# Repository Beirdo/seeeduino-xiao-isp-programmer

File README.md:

seeeduino-xiao-isp-programmer

As I have many Arduino-capable boards in the works, I once again felt the need
for an ISP-based programmer.  I used to use a buspirate, but I don't know 
where it is right now.

This design uses the new Seeeduino XIAO modules.  See:
https://wiki.seeedstudio.com/Seeeduino-XIAO for details.  They are obtainable
very affordably here:
https://www.amazon.com/dp/B08745JBRP/

The v2.0 circuit boards are available to get created at:
https://oshpark.com/shared_projects/VRfrdtNt

I will upload a Digikey-compatible BOM soon, although there are not many parts
here:
* 2 * 10k resistor (0805)
* 1 * MMBT3904 NPN Transistor (SOT23-3)
* 1 * TXB0104PW Bidirectional Level Shifter (TSSOP14)
* 1 * 2x3 0.100" pitch male pin connector for use with a ribbon cable
* 1 * Seeeduino XIAO module (surface mount solder it on using the castellations)

This design is Open Hardware, and the code here is adapted from the ArduinoISP
"example" that comes with the Arduino IDE.  The main changes will be mapping
the IOs for the LEDs correctly, the positive logic reset signal, and the output
enable for the level shifter.

The ISP connector is using 5V signalling, and the XIAO internally uses 3.3V
signalling.  Rather than blow it up over time, I have put in the proper level
shifting on all the data lines (SPI + reset line).  The reset line is using
an open collector setup with a pullup to +5V.  All I/O (at both voltages) are
tristated by default in the level shifter, and are only enabled once the output
enable is driven high (there is a pulldown to make sure it floats low when not
actively being driven).

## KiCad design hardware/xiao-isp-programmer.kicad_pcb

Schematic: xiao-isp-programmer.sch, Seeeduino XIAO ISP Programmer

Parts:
J1: Conn_02x03_Odd_Even; PinHeader_2x03_P2.54mm_Vertical
Q1: MMBT3904; SOT-23
R1, R2: 10k; R_0805_2012Metric_Pad1.20x1.40mm_HandSolder
U1: SeeeduinoXIAO; Seeeduino XIAO-MOUDLE14P-2.54-21X17.8MM
U2: TXB0104PW; TSSOP-14_4.4x5mm_P0.65mm

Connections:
+3V3: U1.12, U2.1 (VCCA)
+5V: J1.2, R1.1, U1.14, U2.14 (VCCB)
GND: J1.6, Q1.2 (E), R2.2, U1.13, U2.7 (GND)
MISO: J1.1, U2.12 (B2)
MOSI: J1.4, U2.13 (B1)
unnamed: Q1.1 (B), U2.10 (B4)
unnamed: U1.9, U2.4 (A3)
unnamed: U1.10, U2.3 (A2)
unnamed: U1.11, U2.2 (A1)
OE: R2.1, U1.3, U2.8 (OE)
RESET: U1.2, U2.5 (A4)
SCK: J1.3, U2.11 (B3)
~RESET: J1.5, Q1.3 (C), R1.2

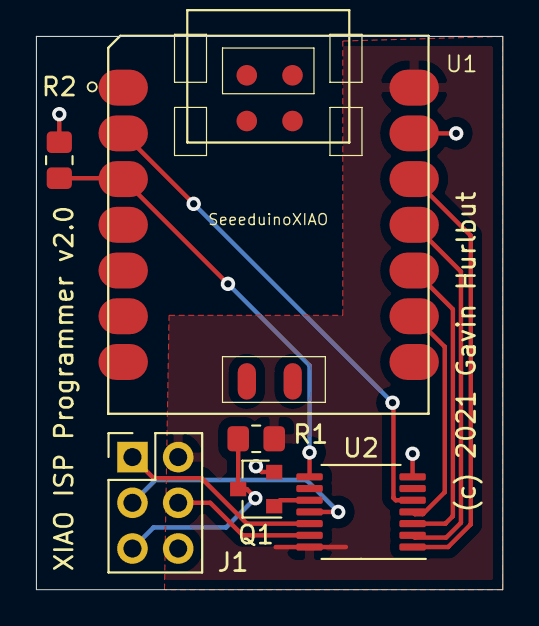
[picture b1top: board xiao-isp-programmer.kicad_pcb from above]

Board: 2 copper layers, 25.9 x 30.7 mm, 6 parts (0 on the bottom side), 13 nets.

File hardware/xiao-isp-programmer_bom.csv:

Reference, Quantity, Value, Footprint, Datasheet
J1 ,1,"Conn_02x03_Odd_Even","Connector_PinHeader_2.54mm:PinHeader_2x03_P2.54mm_Vertical","~"
Q1 ,1,"MMBT3904","Package_TO_SOT_SMD:SOT-23","https://www.onsemi.com/pub/Collateral/2N3903-D.PDF"
R1 R2 ,2,"10k","Resistor_SMD:R_0805_2012Metric_Pad1.20x1.40mm_HandSolder","~"
U1 ,1,"SeeeduinoXIAO","Seeduino:Seeeduino XIAO-MOUDLE14P-2.54-21X17.8MM",""
U2 ,1,"TXB0104PW","Package_SO:TSSOP-14_4.4x5mm_P0.65mm","http://www.ti.com/lit/ds/symlink/txb0104.pdf"

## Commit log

2021-01-02 Add hardware v2.0 design files
    v1.0 had extra LEDs on the board, then I realized the XIAO already has LEDs available, so I removed them and shrunk the board.
2021-01-02 Update README
    Added links to the XIAO module wiki, where to order them on Amazon, and the OSHPark link for the boards.
2021-01-02 Add in the ArduinoISP example code
    Code not modified yet.
2023-02-08 Update to KiCad 6.0, use common libs
2023-02-08 Moved around the firmware too
2023-02-08 Update schematic in doc dir
2023-02-08 Add build selection README.md
2023-02-25 Moved git libraries to new repo
    - https://github.com/Beirdo/KiCad-Git-Libraries

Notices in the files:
hardware/xiao-isp-programmer.kicad_pcb:
(c) 2021 Gavin Hurlbut
